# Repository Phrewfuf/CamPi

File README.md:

CamPi
=====

Raspberry Pi DSLR Controller

Description
===

The aim of this project is to interface my Canon EOS600D
to a Raspberry Pi (i'll check if other ARM devboards work
later on) in order to pull images from the cam and push them
via ftp.

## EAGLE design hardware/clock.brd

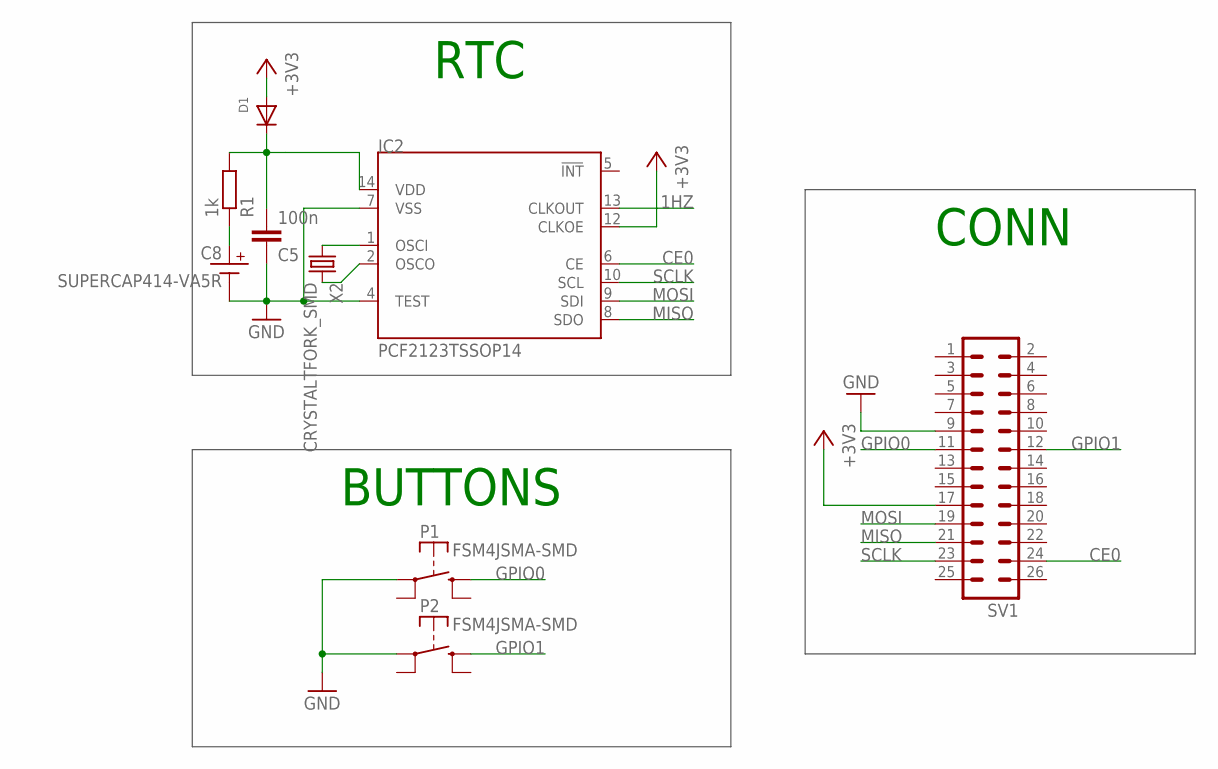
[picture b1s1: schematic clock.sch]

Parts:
C5: 100n; C0603K
C8: SUPERCAP414-VA5R; 414-VA5R
D1: DIODESOD-523; SOD-523
IC2: PCF2123TSSOP14; TSSOP14
P1, P2: FSM4JSMA-SMD
R1: 1k; R0603
SV1: MA13-2
X2: CRYSTALTFORK_SMD; TFORK_SMD

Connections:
1HZ: IC2.13 (CLKOUT)
+3V3: D1.A, IC2.12 (CLKOE), SV1.17
CE0: IC2.6 (CE), SV1.24
GND: C5.1, C8.MINUS, IC2.4 (TEST), IC2.7 (VSS), P1.P$1, P2.P$1, SV1.9
GPIO0: P1.P$3 (S), SV1.11
GPIO1: P2.P$3 (S), SV1.12
MISO: IC2.8 (SDO), SV1.21
MOSI: IC2.9 (SDI), SV1.19
unnamed: IC2.2 (OSCO), X2.3 (2)
unnamed: IC2.1 (OSCI), X2.2 (1)
unnamed: C8.PLUS, R1.1
SCLK: IC2.10 (SCL), SV1.23
VRTC: C5.2, D1.K (C), IC2.14 (VDD), R1.2

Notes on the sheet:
CONN
BUTTONS
RTC

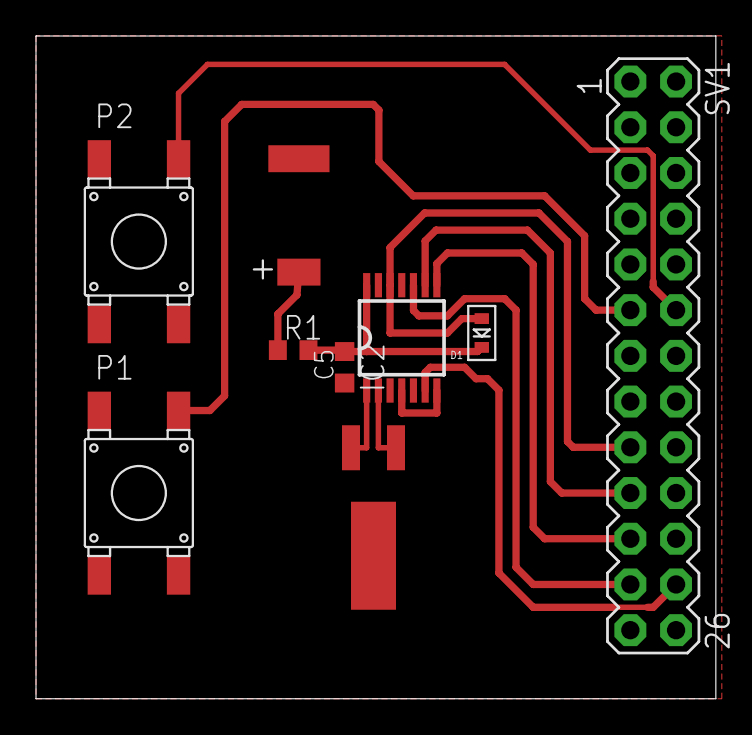
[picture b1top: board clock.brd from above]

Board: 2 copper layers, 37.8 x 36.8 mm, 9 parts (0 on the bottom side), 12 nets.

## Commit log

2013-06-28 started coding Perl script fot cam-polling
2013-07-04 created schematic and layout for RTC/Buttonboard
2013-07-05 changed supercap to a bigger one
2013-07-07 added some example files and libs to work with
2013-07-08 removed campi.pl
2013-07-08 deleted unneeded stuff
